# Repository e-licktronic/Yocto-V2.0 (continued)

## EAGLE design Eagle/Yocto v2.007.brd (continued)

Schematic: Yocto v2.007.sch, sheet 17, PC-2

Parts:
C2: 3n3; C050-025X075
C3, C4, C5, C6: 47n; C050-025X075
C7: 2.2/50; E2-5
C34, C156: 1n; C050-025X075
C36: 220p; C025-025X050
C93: 33/6.3; E2-5
C154: 22n; C050-025X075
C157: 1/50; E2-5
D1, D2: 1N4148; DO35-7C
J4: 22-27-2041-04; 6410-04
Q1, Q2, Q4: 2SC945; TO-92-ECB-PERSO
Q3, Q5: 2SA733; TO-92-ECB-MARKED
Q6: 2SK30; TO-92-MARKED_FET
R1, R46: 1M; 0207/7
R2, R3, R20, R36, R37, R39, R42, R43: 100K; 0207/7
R4, R11, R18, R19, R26: 1K; 0207/7
R5: 220K; 0207/7
R6, R9, R10, R14, R23, R24, R31, R32, R33, R34, R35, R40, R41, R44, R47: 47K; 0207/7
R7, R16, R49, R52: 10K; 0207/7
R8, R17, R22, R29, R53: 22K; 0207/7
R12, R21: 33K; 0207/7
R13: 5K6; 0207/7
R15, R38, R51: 4K7; 0207/7
R25, R45, R60: 470K; 0207/7
R30: 330; 0207/7
R48: 56K; 0207/7
R50: 150K; 0207/7
R58, R59: 100k; 0207/7
SW2, SW3: MSS12; MSS12_SW_SLIDE
TM5: 10K(B); CT6
TP2: TPB0,8; B0,8
U8, U10, U11, U25, U27: µPC4558CA; DIL08
U9: BA6110SIL; SIL09
VR1, VR2, VR3, VR18: 100K(A); R0903N
VR19: 1M(A); R0903N
VR20: 10K(B) CD; R0903N

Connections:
+B9: R1.1, R48.1, U8.8 (V+), U9.9 (V+), U10.8 (V+), U11.8 (V+), U25.8 (V+), U27.8 (V+); also elsewhere on the board
-B9: R50.2, U8.4 (V-), U9.3, U9.5 (V-), U10.4 (V-), U11.4 (V-), U25.4 (V-), U27.4 (V-); also elsewhere on the board
ACCENT_PC2: Q5.E, R51.2; also elsewhere on the board
CP_MA_OUT1: J4.4, R26.1
GND: C4.1, C6.1, C7.-, C34.1, Q1.E, Q2.E, Q3.B, Q4.E, R2.2, R3.2, R8.2, R9.2, R13.2, R16.1, R18.1, R19.1, R21.1, R24.1, R29.2, R30.2, R35.2, R37.2, R38.2, R43.1, R53.1, SW2.P$4, SW2.P$5, SW2.P$6, SW2.P$7, SW3.P$4, SW3.P$5, SW3.P$6, SW3.P$7, TM5.E, U10.3 (+IN), U27.3 (+IN), U27.5 (+IN), VR1.P$4 (C), VR1.P$5 (C), VR2.P$4 (C), VR2.P$5 (C), VR3.1 (A), VR3.P$4 (C), VR3.P$5 (C), VR18.P$4 (C), VR18.P$5 (C), VR19.1 (A), VR19.P$4 (C), VR19.P$5 (C), VR20.P$4 (C), VR20.P$5 (C); also elsewhere on the board
unnamed: D1.A, U8.7 (OUT)
unnamed: D2.A, R1.2
unnamed: Q1.C, R40.1
unnamed: C3.2, Q2.B, R2.1
unnamed: R24.2, U11.3 (+IN)
unnamed: C4.2, C5.2, D2.C, Q2.C
unnamed: C5.1, R3.1, R4.1
unnamed: C36.2, Q6.S, R5.1, R20.1, R25.2, U11.2 (-IN), VR1.1 (A)
unnamed: C6.2, R4.2, R5.2
unnamed: Q3.E, R12.1
unnamed: C36.1, C93.+, R25.1, R26.2, U11.1 (OUT)
unnamed: C7.+, D1.C, R10.2, R11.2, U8.3 (+IN)
unnamed: R7.1, U8.5 (+IN)
unnamed: R9.1, R10.1, U8.6 (-IN)
unnamed: R14.1, SW2.3 (S)
unnamed: C3.1, R12.2, R15.1, R58.2, U8.1 (OUT), U8.2 (-IN)
unnamed: R11.1, VR19.2 (S), VR19.3 (E)
unnamed: Q3.C, U9.4 (C)
unnamed: R15.2, VR20.2 (S)
unnamed: R13.1, R32.2, VR20.1 (A)
unnamed: R19.2, U9.2 (-IN)
unnamed: C34.2, R21.2, U9.6 (OUT), U9.7 (IN1)
unnamed: R20.2, U9.8 (OUT1)
unnamed: R33.2, TM5.S, VR20.3 (E)
unnamed: Q5.B, R51.1, R52.2
unnamed: C157.+, R18.2, U9.1 (+IN)
unnamed: Q4.B, R16.2, R17.1
unnamed: Q4.C, R52.1
unnamed: R34.1, R35.1, U25.3 (+IN)
unnamed: R34.2, R36.1, R38.1, R39.2, TP2.P$1, U25.7 (OUT)
unnamed: R32.1, R36.2, R37.1, U25.6 (-IN)
unnamed: R33.1, U25.5 (+IN), VR3.3 (E), VR18.2 (S)
unnamed: R41.1, U11.6 (-IN)
unnamed: C156.2, R39.1, R40.2, U25.2 (-IN)
unnamed: R42.2, R43.2, U11.5 (+IN)
unnamed: R47.1, VR3.2 (S)
unnamed: Q1.B, R44.2
unnamed: R42.1, R44.1, R46.2, U11.7 (OUT)
unnamed: R47.2, SW2.2
unnamed: R30.1, VR2.1 (A)
unnamed: R49.2, R50.1
unnamed: R49.1, VR18.1 (A)
unnamed: R48.2, VR18.3 (E)
unnamed: R31.1, SW2.1 (O)
unnamed: R45.1, SW3.1 (O)
unnamed: Q5.C, R7.2, R8.1, R53.2
unnamed: R58.1, R59.2, U27.6 (-IN)
unnamed: U27.1 (OUT), U27.2 (-IN)
unnamed: Q6.G, R59.1, R60.2, U27.7 (OUT)
unnamed: C93.-, Q6.D, R60.1, VR1.2 (S)
unnamed: C154.1, R14.2, R22.1, U10.1 (OUT)
unnamed: R22.2, R23.2, U10.5 (+IN)
unnamed: C2.2, R29.1, U10.6 (-IN)
unnamed: C2.1, R23.1, R31.2, U10.7 (OUT), VR2.3 (E)
unnamed: C154.2, R6.1, U10.2 (-IN)
unnamed: R6.2, VR2.2 (S)
unnamed: R46.1, SW3.3 (S)
unnamed: C156.1, R41.2, R45.2, U25.1 (OUT)
unnamed: C157.-, SW3.2
TRIG_PC2: R17.2; also elsewhere on the board

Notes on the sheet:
Adjustment: VR20 center position
1- Set VR18, VR3 and VR2 Full CCW
2- Scope to TP2
3- Set VR20 center position
4- Trig PC2
5- Adjust TM5 to delete ENV

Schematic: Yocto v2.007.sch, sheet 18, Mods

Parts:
MSW1, MSW2: MSS12; MSS12_SW_SLIDE
PAD1, PAD2, PAD3, PAD4, PAD5, PAD6, PAD7, PAD8, PAD9, PAD10, PAD11, PAD12, PAD13, PAD14, PAD15, PAD16, PAD17, PAD18, PAD19, PAD20, PAD21, PAD22, PAD23, PAD24, PAD25, PAD26, PAD27, PAD28, PAD29, PAD30, PAD31, PAD32, PAD33, PAD34, PAD35, PAD36, PAD37, PAD38, PAD39, PAD40, PAD41, PAD42, PAD43, PAD44, PAD45, PAD46, PAD47, PAD48, PAD49, PAD50, PAD51, PAD52, PAD53, PAD54, PAD55, PAD56, PAD57, PAD58, PAD59, PAD60, PAD61, PAD62, PAD63, PAD64, PAD65, PAD66, PAD67, PAD68, PAD69, PAD70, PAD71, PAD72, PAD73, PAD74, PAD75, PAD76, PAD77, PAD78, PAD79, PAD80, PAD81, PAD82, PAD83, PAD84, PAD85, PAD86, PAD87, PAD88, PAD89, PAD90, PAD91, PAD92, PAD93, PAD94, PAD95, PAD96, PAD97, PAD98, PAD99, PAD100, PAD101, PAD102, PAD103, PAD104, PAD105, PAD106, PAD107, PAD108, PAD109, PAD110, PAD111, PAD112, PAD113, PAD114, PAD115, PAD116, PAD117, PAD118, PAD119, PAD120, PAD121, PAD122, PAD123, PAD124, PAD125, PAD126, PAD127, PAD128, PAD129, PAD130, PAD131, PAD132, PAD133, PAD134, PAD135, PAD136, PAD137, PAD138, PAD139, PAD140, PAD141, PAD142, PAD143, PAD144, PAD145, PAD146, PAD147, PAD148, PAD149, PAD150, PAD151, PAD152, PAD153, PAD154, PAD155, PAD156, PAD157, PAD158, PAD159, PAD160, PAD161, PAD162, PAD163, PAD164, PAD165, PAD166, PAD167, PAD168, PAD169, PAD170, PAD171, PAD172, PAD173, PAD174, PAD175, PAD176, PAD177, PAD178, PAD179, PAD180, PAD181, PAD182, PAD183, PAD184, PAD185, PAD186, PAD187, PAD188, PAD189, PAD190, PAD191, PAD192, PAD193, PAD194, PAD195, PAD196, PAD197, PAD198, PAD199, PAD200, PAD201, PAD202, PAD203, PAD204, PAD205, PAD206, PAD207, PAD208, PAD209, PAD210, PAD211, PAD212, PAD213, PAD214, PAD215, PAD216, PAD217, PAD218, PAD219, PAD220, PAD221, PAD222, PAD223, PAD224, PAD225, PAD226, PAD227, PAD228, PAD229, PAD230, PAD231, PAD232, PAD233, PAD234, PAD235, PAD236, PAD237, PAD238, PAD239, PAD240, PAD241, PAD242, PAD243, PAD244, PAD245, PAD246, PAD247, PAD248, PAD249, PAD250, PAD251, PAD252, PAD253, PAD254, PAD255, PAD256, PAD257, PAD258, PAD259, PAD260, PAD261, PAD262, PAD263, PAD264, PAD265, PAD266, PAD267, PAD268, PAD269, PAD270, PAD271, PAD272, PAD273, PAD274, PAD275, PAD276, PAD277, PAD278, PAD279, PAD280, PAD281, PAD282, PAD283, PAD284, PAD285, PAD286, PAD287, PAD288, PAD289, PAD290, PAD291, PAD292, PAD293, PAD294, PAD295, PAD296, PAD297, PAD298, PAD299, PAD300, PAD301, PAD302, PAD303, PAD304, PAD305, PAD306, PAD307, PAD308, PAD309, PAD310, PAD311, PAD312, PAD313, PAD314, PAD315, PAD316, PAD317, PAD318, PAD319, PAD320, PAD321, PAD322, PAD323, PAD324, PAD325, PAD326, PAD327, PAD328, PAD329, PAD330, PAD331, PAD332, PAD333, PAD334, PAD335, PAD336, PAD337, PAD338, PAD339, PAD340, PAD341, PAD342, PAD343, PAD344, PAD345, PAD346, PAD347, PAD348, PAD349, PAD350, PAD351, PAD352, PAD353, PAD354, PAD355, PAD356, PAD357, PAD358, PAD359, PAD360, PAD361, PAD362, PAD363, PAD364, PAD365, PAD366, PAD367, PAD368, PAD369, PAD370, PAD371, PAD372, PAD373, PAD374, PAD375, PAD376, PAD377, PAD378, PAD379, PAD380, PAD381, PAD382, PAD383, PAD384, PAD385, PAD386, PAD387, PAD388, PAD389, PAD390, PAD391, PAD392, PAD393, PAD394, PAD395, PAD396, PAD397, PAD398, PAD399, PAD400, PAD401, PAD402, PAD403, PAD404, PAD405, PAD406, PAD407, PAD408, PAD409, PAD410, PAD411, PAD412, PAD413, PAD414, PAD415, PAD416, PAD417, PAD418, PAD419, PAD420, PAD421, PAD422, PAD423, PAD424, PAD425, PAD426, PAD427, PAD428, PAD429, PAD430, PAD431, PAD432, PAD433, PAD434, PAD435, PAD436, PAD437, PAD438, PAD439, PAD440, PAD441, PAD442, PAD443, PAD444, PAD446, PAD447, PAD448, PAD449, PAD450, PAD451, PAD452, PAD453, PAD454, PAD455, PAD456, PAD458, PAD459, PAD460, PAD461, PAD462, PAD463, PAD464, PAD465, PAD466, PAD467, PAD468, PAD470, PAD471, PAD472, PAD473, PAD474, PAD475, PAD476, PAD477, PAD478, PAD479, PAD480, PAD482, PAD483, PAD484, PAD485, PAD486, PAD487, PAD488, PAD489, PAD490, PAD491, PAD492, PAD494, PAD495, PAD496, PAD497, PAD498, PAD499, PAD500, PAD501, PAD502, PAD503, PAD506, PAD507, PAD508, PAD509, PAD510, PAD511, PAD512, PAD513, PAD514, PAD515, PAD518, PAD519, PAD520, PAD521, PAD522, PAD523, PAD524, PAD525, PAD526, PAD527, PAD530, PAD531, PAD532, PAD533, PAD534, PAD535, PAD536, PAD537, PAD538, PAD539, PAD542, PAD543, PAD544, PAD545, PAD546, PAD547, PAD548, PAD549, PAD550, PAD551: 1,6/0,8; 1.6/0.8ROUND

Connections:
+15V: PAD334.1, PAD335.1, PAD338.1; also elsewhere on the board
-15V: PAD287.1, PAD288.1, PAD292.1, PAD297.1; also elsewhere on the board
GND: PAD207.1, PAD213.1, PAD214.1, PAD220.1, PAD221.1, PAD227.1, PAD228.1, PAD241.1, PAD242.1, PAD261.1, PAD296.1, PAD301.1, PAD446.1, PAD458.1, PAD470.1, PAD475.1, PAD487.1, PAD499.1; also elsewhere on the board
unnamed: MSW1.1 (O), PAD326.1
unnamed: MSW1.3 (S), PAD327.1
unnamed: MSW2.1 (O), PAD330.1
unnamed: MSW2.3 (S), PAD331.1
unnamed: MSW2.2, PAD329.1
unnamed: MSW1.2, PAD328.1
PSU_+15: PAD410.1, PAD415.1, PAD422.1, PAD427.1, PAD434.1, PAD439.1; also elsewhere on the board
PSU_-15: PAD432.1, PAD494.1, PAD506.1, PAD518.1, PAD535.1, PAD547.1; also elsewhere on the board

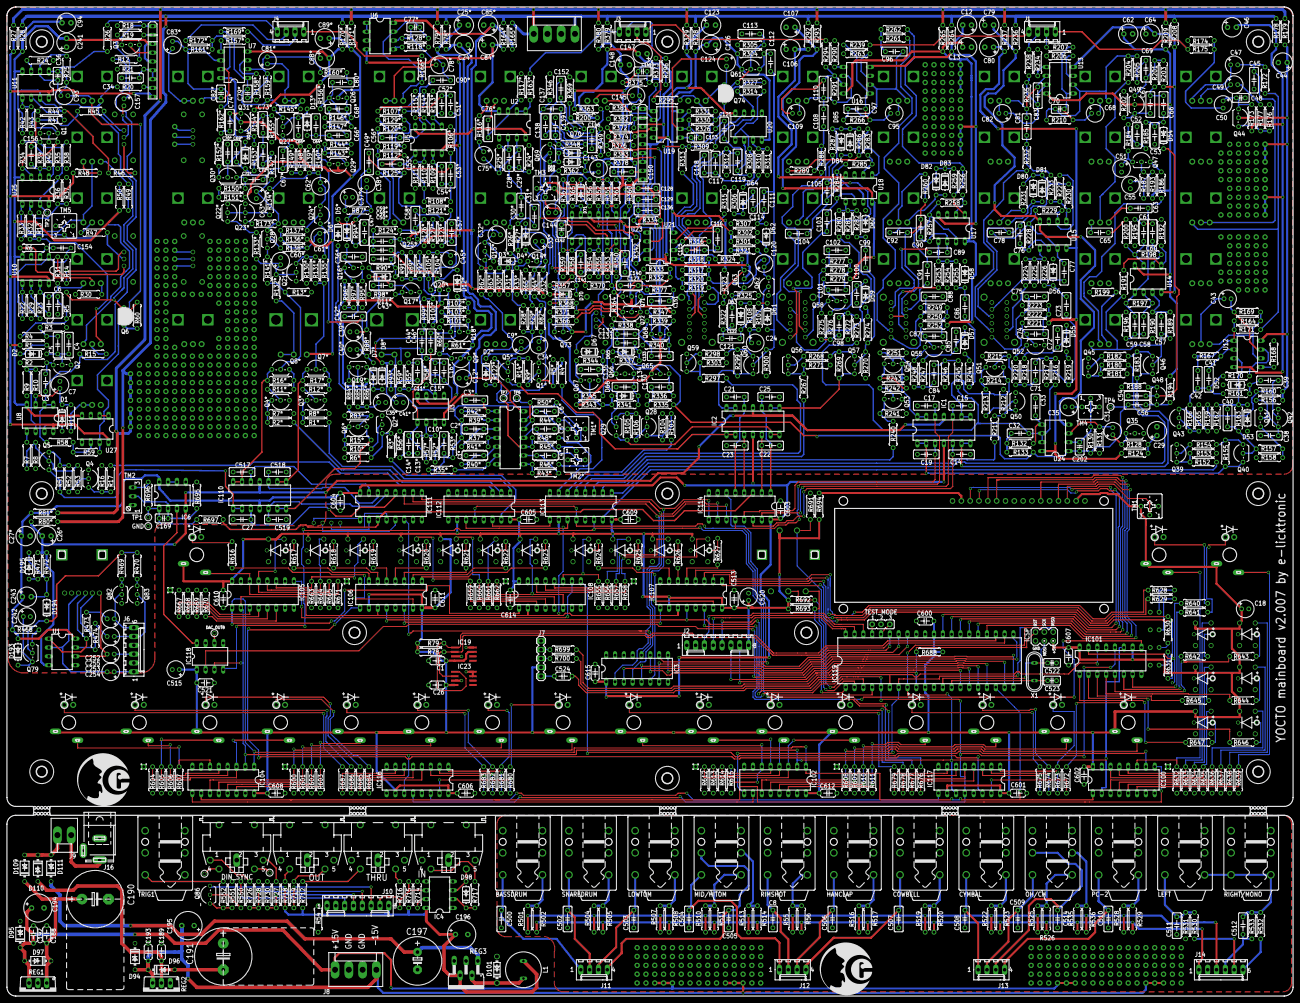
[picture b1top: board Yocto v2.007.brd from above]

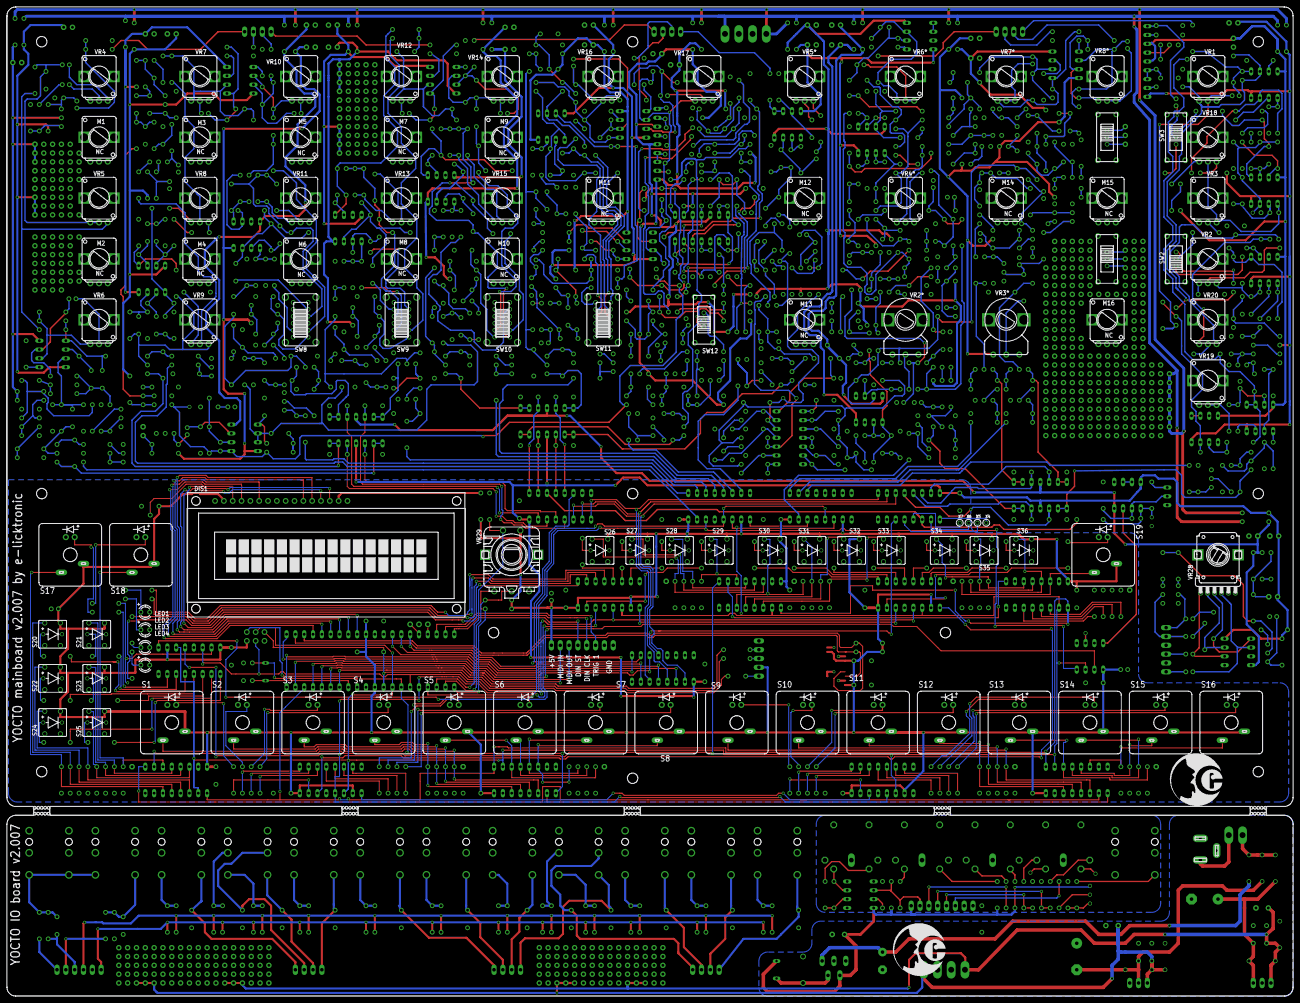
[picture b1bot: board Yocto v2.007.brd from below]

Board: 2 copper layers, 370.0 x 284.6 mm, 1765 parts (101 on the bottom side), 817 nets.

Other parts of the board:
U$1, U$13, U$14, U$15: LOGO_15MM_LITE
U$2, U$3, U$4, U$5, U$6, U$7, U$8, U$9, U$10, U$11, U$12: 3,0

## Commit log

2022-08-23 Create Eagle
